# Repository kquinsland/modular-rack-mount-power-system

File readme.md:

# Modular Rack Power

This is a "side-quest" project on the way to building a small "mini rack" dedicated to hosting GH/A runners.

I'll do the CAD and standalone development here before integrating it into the larger project.
The goal is to have a modular system of a backplane and multiple carrier modules that can be swapped in and out to provide different power configurations as needed.
As long as the power supply can handle it, backplanes may share/daisy-chain the
input distribution needed by their carrier modules.

Hardware, firmware, and host tooling for a modular mini-rack power system.

## Boards

- `backplane`: STM32C092/CAN-FD backplane with six carrier slots, power
  distribution, aggregate current monitoring, fan control, and a status
  NeoPixel.
- `carrier`: Mates with one backplane slot and hosts an SW3538 USB-C PD module.

Every backplane and carrier is an independent STM32C092 CAN-FD node. There is no
I2C mux and no controller/proxy relationship between nodes. Earlier hardware and
firmware were research prototypes and are not compatibility targets.

## Layout

```text
firmware/
  Cargo.toml
  backplane/
  carrier/
  bootloader/
  crates/
  tools/
  xtask/
  docs/pdcan/
hardware/
  boards/
    backplane/
    carrier/
  libraries/
    symbols/
    footprints/
    3dmodels/
  mechanical/
docs/
scripts/
build/
releases/
```

`build/` is for generated local outputs. `releases/` is for fabrication packages that should be preserved exactly as sent to a board house.

See [`firmware/README.md`](firmware/README.md) for workspace commands and the
current hardware/firmware contract. Run `mise run firmware:check` from this
directory, or run Cargo commands from `firmware/`. The reviewed implementation
plan is kept in [`firmware/plan.md`](firmware/plan.md).

## Documentation site

The public-facing project documentation is maintained in [`site/`](site/) and
is intended for <https://mrps.karlquinsland.com/>. Run `mise run site:serve` for
local preview or `mise run site:build` for a production build. Create journal
entries with `mise run worklog:new -- "Concise Summary"` to create
`site/content/worklogs/YYYY/MM/DD - Concise Summary/index.md` with matching
front matter and an adjacent `_files/` directory for page resources.

## Misc

I can't believe that it's STILL such a pain in the ass to use LCSC to search for parts that are stocked by the SMT service.
https://yaqwsx.github.io/jlcparts/#/

Also super useful reference: https://www.tinkervault.com/usb-power-sources/dc-pd30-adapters
It's how I 'caught' that the `sw3538` based module I am using is non-standard 140W, later confirmed:

- https://en.eeworld.com.cn/Reference_Designs/detail/81702
- https://github.com/happyme531/h1_SW35xx/issues/13#issuecomment-4361605621

https://github.com/Shrike-Lab/HomeLab-PDU-V1/blob/main/ASSEMBLY/README.md#pcb-tray

Plan was to use APK43070 but they do not support MCU controlling it via i2c

https://meron33.hatenablog.com/entry/2026/02/07/112759

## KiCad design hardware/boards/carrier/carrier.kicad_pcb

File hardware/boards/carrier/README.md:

# Carrier PCB

KiCad project for one mini-rack power carrier board.

Responsibilities:

- Mate with one backplane slot.
- Host one fixed-address DC/USB-C PD module.
- Convert the slot-local DC and CAN-FD interface into the module-local wiring.
- Keep carrier-side interfaces reusable across all backplane slots.

Assembly notes:

- `J1` and `MOD1` are intentionally DNP/excluded from the PCB assembly BOM. The
  user installs and solders the right-angle XT30PW(2+2) connector and SW3538
  module after assembly.
- The housekeeping converter shares the backplane's LM5164DDAR regulator and
  PSPMAA0805-101M-ANP 100 µH inductor.
- L1 is placed and routed. The checked-in assembly and fabrication outputs are
  generated and validated with `mise run production:carrier`.

Relevant docs:

- `../../../docs/system-overview.md`
- `../../../docs/interfaces.md`
- `../../../docs/power-budget.md`
- `hardware-handoff.md`

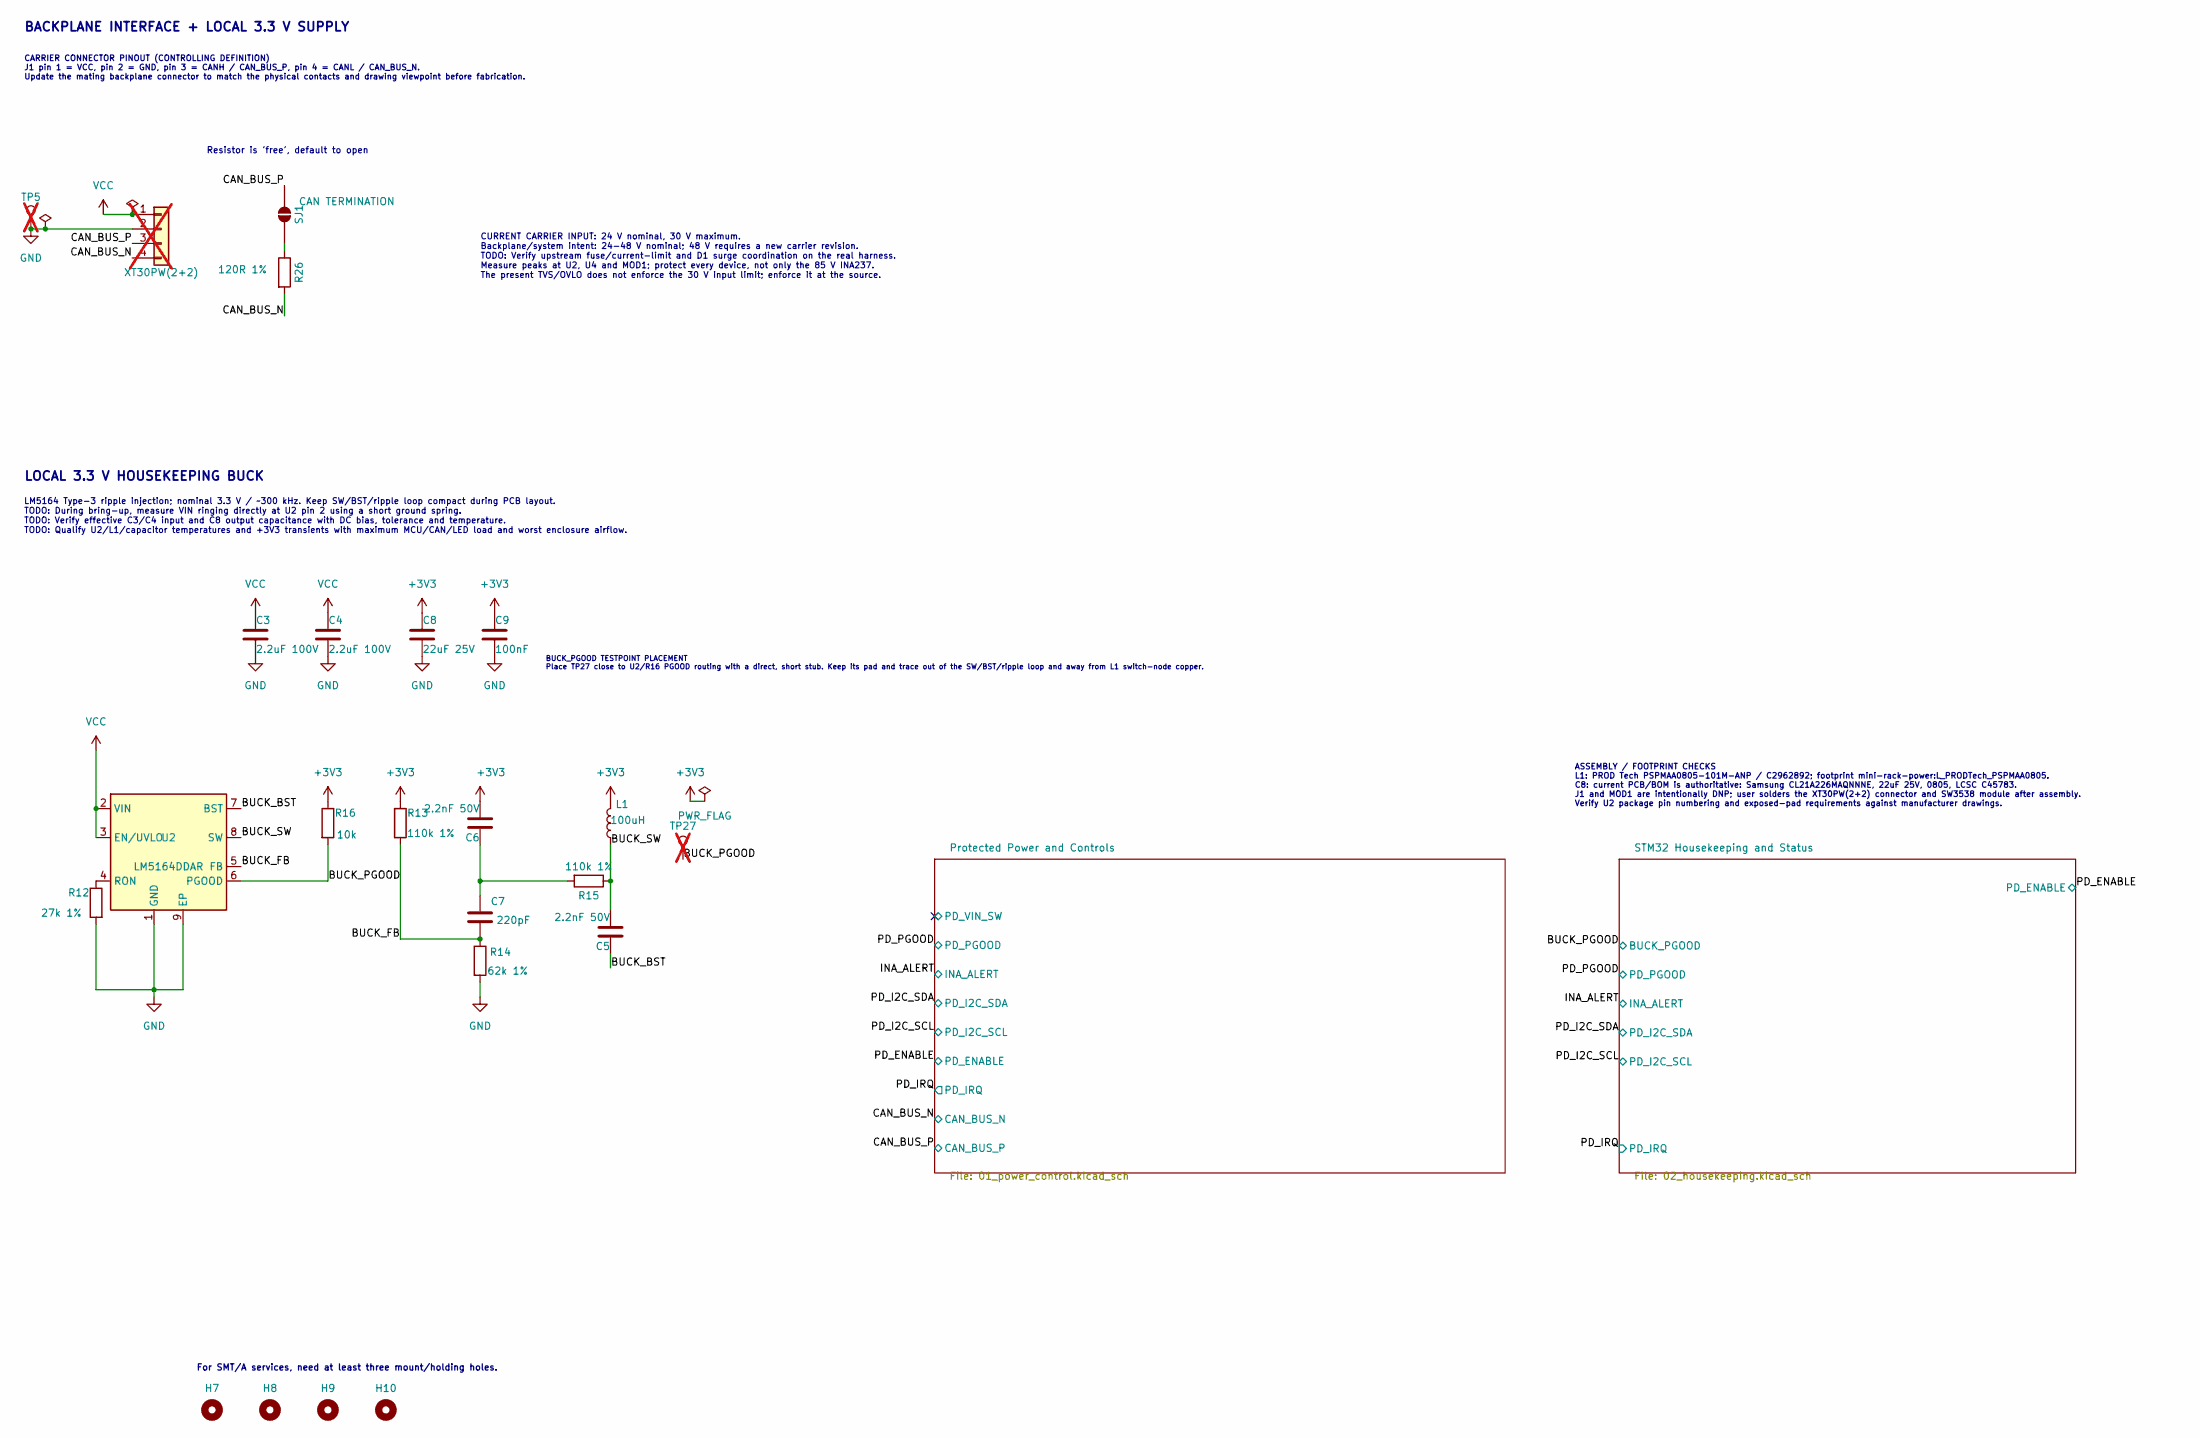
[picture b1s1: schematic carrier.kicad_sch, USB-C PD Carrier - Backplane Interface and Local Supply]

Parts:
C3, C4: 2.2uF 100V; C_1210_3225Metric; MPN CL32B225KCJSNNE; LCSC C55151
C5, C6: 2.2nF 50V; C_0603_1608Metric; MPN 0603B222K500NT; LCSC C1604
C7: 220pF; C_0603_1608Metric; MPN CC0603JRNPO9BN221; LCSC C106210
C8: 22uF 25V; C_0805_2012Metric; MPN CL21A226MAQNNNE; LCSC C45783
C9: 100nF; C_0603_1608Metric; MPN CC0603KRX7R9BB104; LCSC C14663
H7, H8, H9, H10: ToolingHole_1.152mm; MountingHole_JLCPCB_Tooling_1.152mm
J1: XT30PW(2+2); Amass_XT30PW_2plus2_M_RightAngle_THT; MPN XT30PW(2+2)-M.G.B; LCSC C19268030; not fitted
L1: 100uH; L_PRODTech_PSPMAA0805; MPN PSPMAA0805-101M-ANP; LCSC C2962892
R12: 27k 1%; R_0603_1608Metric; MPN 0603WAF2702T5E; LCSC C22967
R13, R15: 110k 1%; R_0603_1608Metric; MPN 0603WAF1103T5E; LCSC C25805
R14: 62k 1%; R_0603_1608Metric; MPN 0603WAF6202T5E; LCSC C23221
R16: 10k; R_0603_1608Metric; MPN 0603WAF1002T5E; LCSC C25804
R26: 120R 1%; R_0603_1608Metric; MPN 0603WAF1200T5E; LCSC C22787
SJ1: CAN TERMINATION; SolderJumper-2_P1.3mm_Open_Pad1.0x1.5mm; MPN PCB feature
TP5: GND; TestPoint_Pad_D1.0mm; not fitted
TP27: BUCK_PGOOD; TestPoint_Pad_D1.5mm; MPN PCB test point; not fitted
U2: LM5164DDAR; TI_SO-PowerPAD-8; MPN LM5164DDAR; LCSC C477928

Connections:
+3V3: C6.2, C8.1, C9.1, L1.2, R13.1, R16.1; also elsewhere on the board
/BUCK_BST: C5.1, U2.7 (BST)
/BUCK_FB: C7.2, R13.2, R14.1, U2.5 (FB)
/BUCK_PGOOD: R16.2, TP27.1 (1_1), U2.6 (PGOOD); also elsewhere on the board
/BUCK_SW: C5.2, L1.1, R15.1, U2.8 (SW)
/CAN_BUS_N: J1.4, R26.2; also elsewhere on the board
/CAN_BUS_P: J1.3, SJ1.1 (A); also elsewhere on the board
GND: C3.2, C4.2, C8.2, C9.2, J1.2, R12.2, R14.2, TP5.1 (1_1), U2.1 (GND), U2.9 (EP); also elsewhere on the board
unnamed: C6.1, C7.1, R15.2
unnamed: R26.1, SJ1.2 (B)
unnamed: R12.1, U2.4 (RON)
VCC: C3.1, C4.1, J1.1, U2.2 (VIN), U2.3 (EN/UVLO); also elsewhere on the board

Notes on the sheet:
CURRENT CARRIER INPUT: 24 V nominal, 30 V maximum. Backplane/system intent: 24-48 V nominal; 48 V requires a new carrier revision. TODO: Verify upstream fuse/current-limit and D1 surge coordination on the real harness. Measure peaks at U2, U4 and MOD1; protect every device, not only the 85 V INA237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
LOCAL 3.3 V HOUSEKEEPING BUCK
ASSEMBLY / FOOTPRINT CHECKS L1: PROD Tech PSPMAA0805-101M-ANP / C2962892; footprint mini-rack-power:L_PRODTech_PSPMAA0805. C8: current PCB/BOM is authoritative: Samsung CL21A226MAQNNNE, 22uF 25V, 0805, LCSC C45783. J1 and MOD1 are intentionally DNP; user solders the XT30PW(2+2) connector and SW3538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
Resistor is 'free', default to open
LM5164 Type-3 ripple injection; nominal 3.3 V / ~300 kHz. Keep SW/BST/ripple loop compact during PCB layout. TODO: During bring-up, measure VIN ringing directly at U2 pin 2 using a short ground spring. TODO: Verify effective C3/C4 input and C8 output capacitance with DC bias, tolerance and temperat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
BUCK_PGOOD TESTPOINT PLACEMENT Place TP27 close to U2/R16 PGOOD routing with a direct, short stub. Keep its pad and trace out of the SW/BST/ripple loop and away from L1 switch-node copper.
For SMT/A services, need at least three mount/holding holes.
CARRIER CONNECTOR PINOUT (CONTROLLING DEFINITION) J1 pin 1 = VCC, pin 2 = GND, pin 3 = CANH / CAN_BUS_P, pin 4 = CANL / CAN_BUS_N. Update the mating backplane connector to match the physical contacts and drawing viewpoint before fabrication.
BACKPLANE INTERFACE + LOCAL 3.3 V SUPPLY

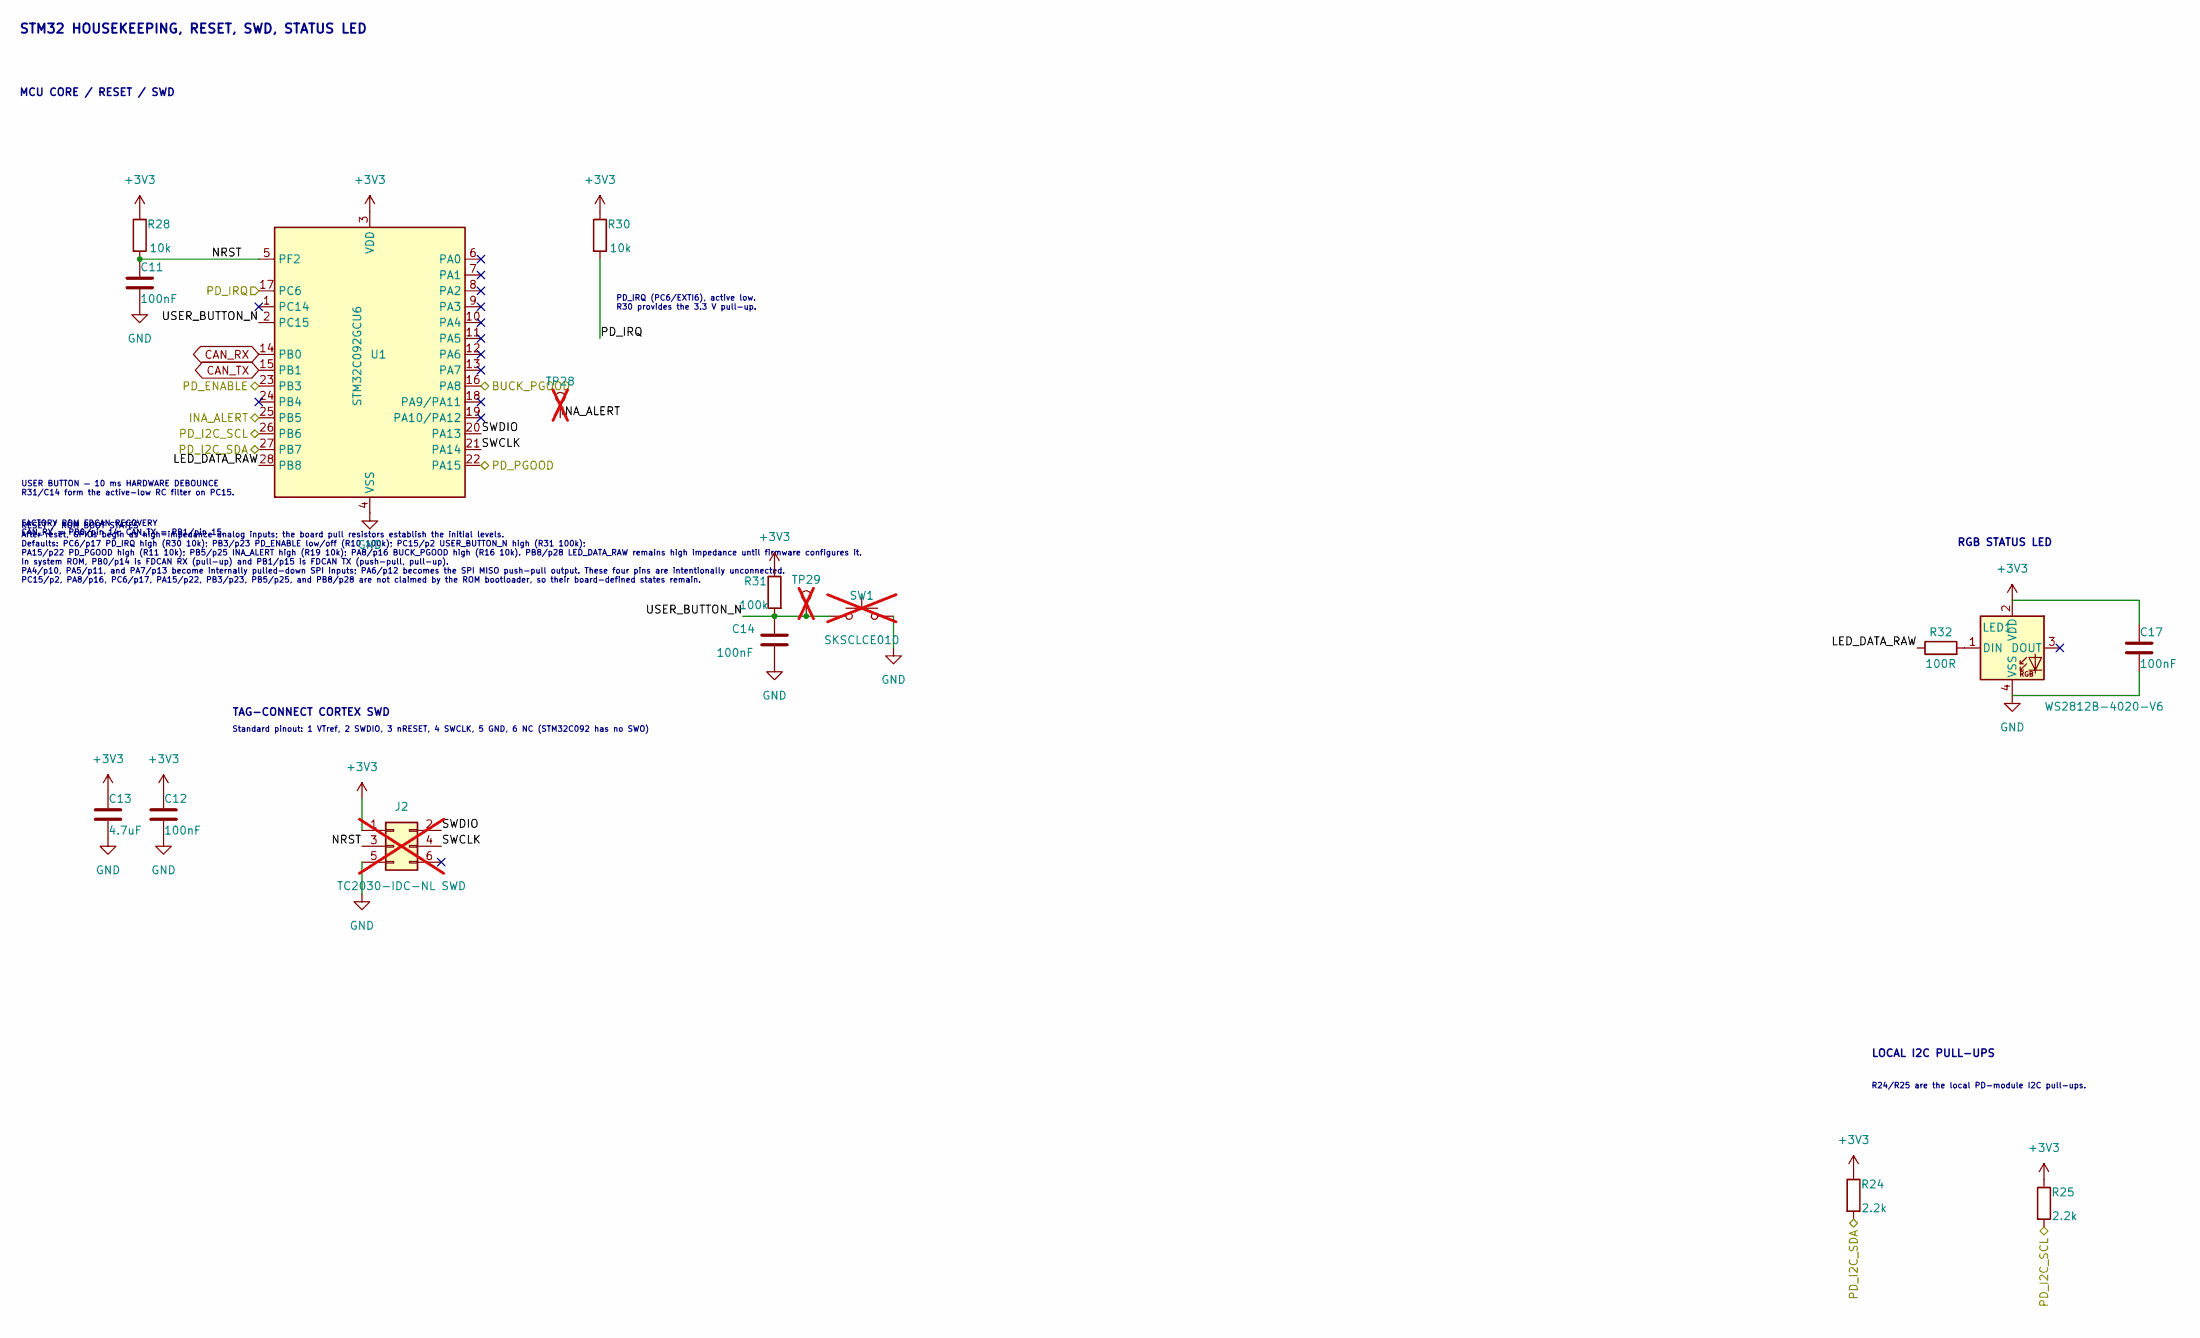
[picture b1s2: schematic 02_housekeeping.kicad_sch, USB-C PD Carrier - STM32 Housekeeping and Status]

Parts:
C11, C12, C14, C17: 100nF; C_0603_1608Metric; MPN CC0603KRX7R9BB104; LCSC C14663
C13: 4.7uF; C_0603_1608Metric; MPN CL10A475KO8NNNC; LCSC C19666
J2: TC2030-IDC-NL SWD; Tag-Connect_TC2030-IDC-NL_2x03_P1.27mm_Vertical; MPN TC2030-IDC-NL; not fitted
LED1: WS2812B-4020-V6; LED_Worldsemi_WS2812B-4020-V6_SideView; MPN WS2812B-4020-V6; LCSC C52941387
R24, R25: 2.2k; R_0603_1608Metric; MPN 0603WAF2201T5E; LCSC C4190
R28, R30: 10k; R_0603_1608Metric; MPN 0603WAF1002T5E; LCSC C25804
R31: 100k; R_0603_1608Metric; MPN 0603WAF1003T5E; LCSC C25803
R32: 100R; R_0603_1608Metric; MPN 0603WAF1000T5E; LCSC C22775
SW1: SKSCLCE010; SW_ALPS_SKSCLCE010_SidePush; MPN SKSCLCE010; LCSC C139799; not fitted
TP28: INA_ALERT; TestPoint_Pad_D1.5mm; MPN PCB test point; not fitted
TP29: USER_BUTTON_N; TestPoint_Pad_D1.5mm; MPN PCB test point; not fitted
U1: STM32C092GCU6; QFN-28_4x4mm_P0.5mm; MPN STM32C092GCU6; LCSC C44847705

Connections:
+3V3: C12.1, C13.1, C17.1, J2.1, LED1.2 (VDD), R24.1, R25.1, R28.1, R30.1, R31.1, U1.3 (VDD); also elsewhere on the board
/BUCK_PGOOD: U1.16 (PA8); also elsewhere on the board
/INA_ALERT: TP28.1 (1_1), U1.25 (PB5); also elsewhere on the board
/PD_ENABLE: U1.23 (PB3); also elsewhere on the board
/PD_I2C_SCL: R25.2, U1.26 (PB6); also elsewhere on the board
/PD_I2C_SDA: R24.2, U1.27 (PB7); also elsewhere on the board
/PD_IRQ: R30.2, U1.17 (PC6); also elsewhere on the board
/PD_PGOOD: U1.22 (PA15); also elsewhere on the board
/STM32 Housekeeping and Status/LED_DATA_RAW: R32.1, U1.28 (PB8)
/STM32 Housekeeping and Status/NRST: C11.1, J2.3, R28.2, U1.5 (PF2)
/STM32 Housekeeping and Status/SWCLK: J2.4, U1.21 (PA14)
/STM32 Housekeeping and Status/SWDIO: J2.2, U1.20 (PA13)
/STM32 Housekeeping and Status/USER_BUTTON_N: C14.1, R31.2, SW1.2, TP29.1 (1_1), U1.2 (PC15)
CAN_RX: U1.14 (PB0); also elsewhere on the board
CAN_TX: U1.15 (PB1); also elsewhere on the board
GND: C11.2, C12.2, C13.2, C14.2, C17.2, J2.5, LED1.4 (VSS), SW1.1, U1.4 (VSS); also elsewhere on the board
unnamed: LED1.1 (DIN), R32.2

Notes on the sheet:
Standard pinout: 1 VTref, 2 SWDIO, 3 nRESET, 4 SWCLK, 5 GND, 6 NC (STM32C092 has no SWO)
FACTORY ROM FDCAN RECOVERY CAN_RX = PB0/pin 14; CAN_TX = PB1/pin 15.
LOCAL I2C PULL-UPS
USER BUTTON — 10 ms HARDWARE DEBOUNCE R31/C14 form the active-low RC filter on PC15.
R24/R25 are the local PD-module I2C pull-ups.
TAG-CONNECT CORTEX SWD
MCU CORE / RESET / SWD
STM32 HOUSEKEEPING, RESET, SWD, STATUS LED
PD_IRQ (PC6/EXTI6), active low. R30 provides the 3.3 V pull-up.
RESET / ROM BOOT STATES After reset, GPIOs begin as high-impedance analog inputs; the board pull resistors establish the initial levels. Defaults: PC6/p17 PD_IRQ high (R30 10k); PB3/p23 PD_ENABLE low/off (R10 100k); PC15/p2 USER_BUTTON_N high (R31 100k); PA15/p22 PD_PGOOD high (R11 10k); PB5/p25 IN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
RGB STATUS LED

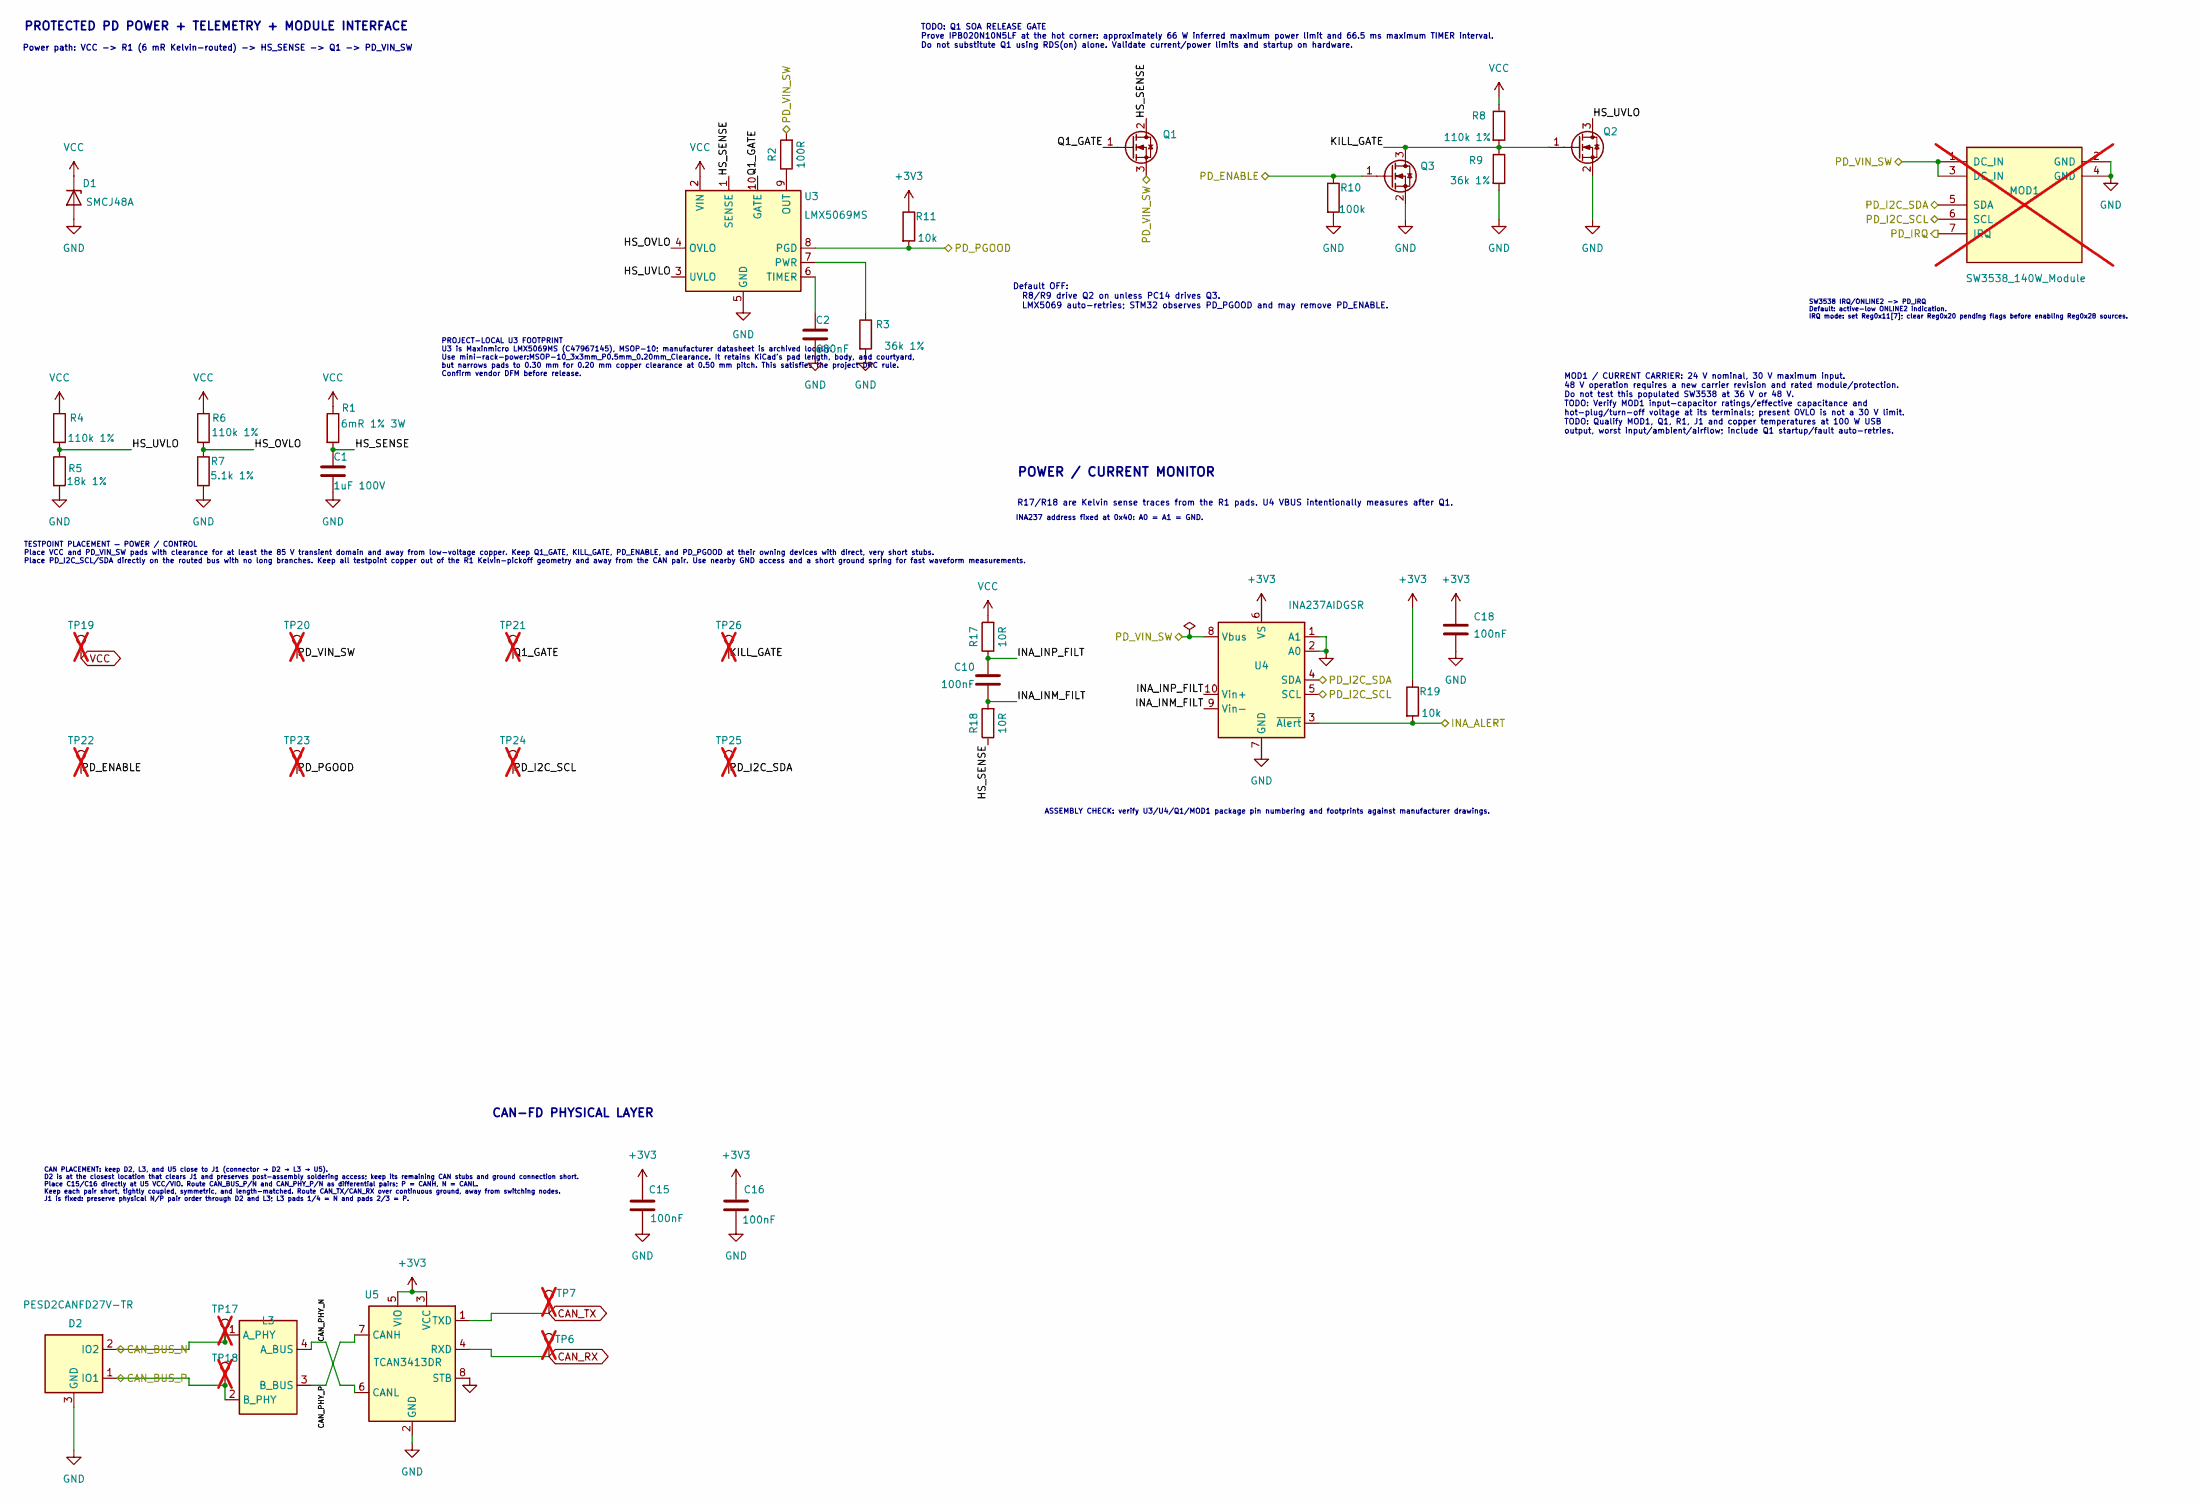
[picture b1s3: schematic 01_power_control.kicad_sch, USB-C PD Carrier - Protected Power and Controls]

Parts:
C1: 1uF 100V; C_1206_3216Metric; MPN CL31B105KCHNNNE; LCSC C13832
C2: 680nF; C_0603_1608Metric; MPN 0603B684K160NT; LCSC C24797
C10, C15, C16, C18: 100nF; C_0603_1608Metric; MPN CC0603KRX7R9BB104; LCSC C14663
D1: SMCJ48A; D_SMC_Silk0.15mm; MPN SMCJ48A; LCSC C19077611
D2: PESD2CANFD27V-TR; SOT-23; MPN PESD2CANFD27V-TR; LCSC C552488
L3: ACT1210D-101-2P-TL00; L_CommonModeChoke_TDK_ACT1210D; MPN ACT1210D-101-2P-TL00; LCSC C3039743
MOD1: SW3538_140W_Module; not fitted
Q1: IPB020N10N5LF; TO-263-3_TabPin2; MPN IPB020N10N5LF; LCSC C536484
Q2, Q3: 2N7002; SOT-23; MPN 2N7002; LCSC C8545
R1: 6mR 1% 3W; R_2512_6332Metric; MPN HoLLR2512-3W-6mR-1%; LCSC C2985709
R2: 100R; R_0603_1608Metric; MPN 0603WAF1000T5E; LCSC C22775
R3, R9: 36k 1%; R_0603_1608Metric; MPN 0603WAF3602T5E; LCSC C23147
R4, R6, R8: 110k 1%; R_0603_1608Metric; MPN 0603WAF1103T5E; LCSC C25805
R5: 18k 1%; R_0603_1608Metric; MPN 0603WAF1802T5E; LCSC C25810
R7: 5.1k 1%; R_0603_1608Metric; MPN 0603WAF5101T5E; LCSC C23186
R10: 100k; R_0603_1608Metric; MPN 0603WAF1003T5E; LCSC C25803
R11, R19: 10k; R_0603_1608Metric; MPN 0603WAF1002T5E; LCSC C25804
R17, R18: 10R; R_0603_1608Metric; MPN 0603WAF100JT5E; LCSC C22859
TP6: CAN_RX; TestPoint_Pad_D1.5mm; MPN PCB test point; not fitted
TP7: CAN_TX; TestPoint_Pad_D1.5mm; MPN PCB test point; not fitted
TP17: CAN_BUS_N; TestPoint_Pad_D1.5mm; MPN PCB test point; not fitted
TP18: CAN_BUS_P; TestPoint_Pad_D1.5mm; MPN PCB test point; not fitted
TP19: VCC; TestPoint_Pad_D1.5mm; MPN PCB test point; not fitted
TP20: PD_VIN_SW; TestPoint_Pad_D1.5mm; MPN PCB test point; not fitted
TP21: Q1_GATE; TestPoint_Pad_D1.5mm; MPN PCB test point; not fitted
TP22: PD_ENABLE; TestPoint_Pad_D1.5mm; MPN PCB test point; not fitted
TP23: PD_PGOOD; TestPoint_Pad_D1.5mm; MPN PCB test point; not fitted
TP24: PD_I2C_SCL; TestPoint_Pad_D1.5mm; MPN PCB test point; not fitted
TP25: PD_I2C_SDA; TestPoint_Pad_D1.5mm; MPN PCB test point; not fitted
TP26: KILL_GATE; TestPoint_Pad_D1.5mm; MPN PCB test point; not fitted
U3: LMX5069MS; MSOP-10_3x3mm_P0.5mm_0.20mm_Clearance; MPN LMX5069MS; LCSC C47967145
U4: INA237AIDGSR; TSSOP-10_3x3mm_P0.5mm; MPN INA237AIDGSR; LCSC C2864837
U5: TCAN3413DR; SOIC-8_3.9x4.9mm_P1.27mm; MPN TCAN3413DR; LCSC C22433320

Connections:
+3V3: C15.1, C16.1, C18.1, R11.1, R19.1, U4.6 (VS), U5.3 (VCC), U5.5 (VIO); also elsewhere on the board
/CAN_BUS_N: D2.2 (IO2), L3.1 (A_PHY), TP17.1 (1_1); also elsewhere on the board
/CAN_BUS_P: D2.1 (IO1), L3.2 (B_PHY), TP18.1 (1_1); also elsewhere on the board
/INA_ALERT: R19.2, U4.3 (~Alert); also elsewhere on the board
/PD_ENABLE: Q3.1 (G), R10.1, TP22.1 (1_1); also elsewhere on the board
/PD_I2C_SCL: MOD1.6 (SCL), TP24.1 (1_1), U4.5 (SCL); also elsewhere on the board
/PD_I2C_SDA: MOD1.5 (SDA), TP25.1 (1_1), U4.4 (SDA); also elsewhere on the board
/PD_IRQ: MOD1.7 (IRQ); also elsewhere on the board
/PD_PGOOD: R11.2, TP23.1 (1_1), U3.8 (PGD); also elsewhere on the board
/Protected Power and Controls/CAN_PHY_N: L3.4 (A_BUS), U5.6 (CANL)
/Protected Power and Controls/CAN_PHY_P: L3.3 (B_BUS), U5.7 (CANH)
/Protected Power and Controls/HS_OVLO: R6.2, R7.1, U3.4 (OVLO)
/Protected Power and Controls/HS_SENSE: C1.1, Q1.2 (D), R1.2, R18.1, U3.1 (SENSE)
/Protected Power and Controls/HS_UVLO: Q2.3 (D), R4.2, R5.1, U3.3 (UVLO)
/Protected Power and Controls/INA_INM_FILT: C10.2, R18.2, U4.9 (Vin-)
/Protected Power and Controls/INA_INP_FILT: C10.1, R17.1, U4.10 (Vin+)
/Protected Power and Controls/KILL_GATE: Q2.1 (G), Q3.3 (D), R8.2, R9.1, TP26.1 (1_1)
/Protected Power and Controls/PD_VIN_SW: MOD1.1 (DC_IN), MOD1.3 (DC_IN), Q1.3 (S), R2.2, TP20.1 (1_1), U4.8 (Vbus)
/Protected Power and Controls/Q1_GATE: Q1.1 (G), TP21.1 (1_1), U3.10 (GATE)
CAN_RX: TP6.1 (1_1), U5.4 (RXD); also elsewhere on the board
CAN_TX: TP7.1 (1_1), U5.1 (TXD); also elsewhere on the board
GND: C1.2, C2.2, C15.2, C16.2, C18.2, D1.2 (A), D2.3 (GND), MOD1.2 (GND), MOD1.4 (GND), Q2.2 (S), Q3.2 (S), R3.2, R5.2, R7.2, R9.2, R10.2, U3.5 (GND), U4.1 (A1), U4.2 (A0), U4.7 (GND), U5.2 (GND), U5.8 (STB); also elsewhere on the board
unnamed: R2.1, U3.9 (OUT)
unnamed: R3.1, U3.7 (PWR)
unnamed: C2.1, U3.6 (TIMER)
VCC: D1.1 (K), R1.1, R4.1, R6.1, R8.1, R17.2, TP19.1 (1_1), U3.2 (VIN); also elsewhere on the board

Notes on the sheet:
MOD1 / CURRENT CARRIER: 24 V nominal, 30 V maximum input. 48 V operation requires a new carrier revision and rated module/protection. Do not test this populated SW3538 at 36 V or 48 V. TODO: Verify MOD1 input-capacitor ratings/effective capacitance and hot-plug/turn-off voltage at its terminals; pr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
PROTECTED PD POWER + TELEMETRY + MODULE INTERFACE
INA237 address fixed at 0x40: A0 = A1 = GND.
TODO: Q1 SOA RELEASE GATE Prove IPB020N10N5LF at the hot corner: approximately 66 W inferred maximum power limit and 66.5 ms maximum TIMER interval. Do not substitute Q1 using RDS(on) alone. Validate current/power limits and startup on hardware.
R17/R18 are Kelvin sense traces from the R1 pads. U4 VBUS intentionally measures after Q1.
TESTPOINT PLACEMENT — POWER / CONTROL Place VCC and PD_VIN_SW pads with clearance for at least the 85 V transient domain and away from low-voltage copper. Keep Q1_GATE, KILL_GATE, PD_ENABLE, and PD_PGOOD at their owning devices with direct, very short stubs. Place PD_I2C_SCL/SDA directly on the rou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
PROJECT-LOCAL U3 FOOTPRINT U3 is Maxinmicro LMX5069MS (C47967145), MSOP-10; manufacturer datasheet is archived locally. Use mini-rack-power:MSOP-10_3x3mm_P0.5mm_0.20mm_Clearance. It retains KiCad's pad length, body, and courtyard, but narrows pads to 0.30 mm for 0.20 mm copper clearance at 0.50 mm 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
Default OFF: R8/R9 drive Q2 on unless PC14 drives Q3. LMX5069 auto-retries; STM32 observes PD_PGOOD and may remove PD_ENABLE.
CAN-FD PHYSICAL LAYER
CAN PLACEMENT: keep D2, L3, and U5 close to J1 (connector → D2 → L3 → U5). D2 is at the closest location that clears J1 and preserves post-assembly soldering access; keep its remaining CAN stubs and ground connection short. Place C15/C16 directly at U5 VCC/VIO. Route CAN_BUS_P/N and CAN_PHY_P/N as 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
SW3538 IRQ/ONLINE2 -> PD_IRQ Default: active-low ONLINE2 indication. IRQ mode: set Reg0x11[7]; clear Reg0x20 pending flags before enabling Reg0x28 sources.
ASSEMBLY CHECK: verify U3/U4/Q1/MOD1 package pin numbering and footprints against manufacturer drawings.
Power path: VCC -> R1 (6 mR Kelvin-routed) -> HS_SENSE -> Q1 -> PD_VIN_SW
POWER / CURRENT MONITOR

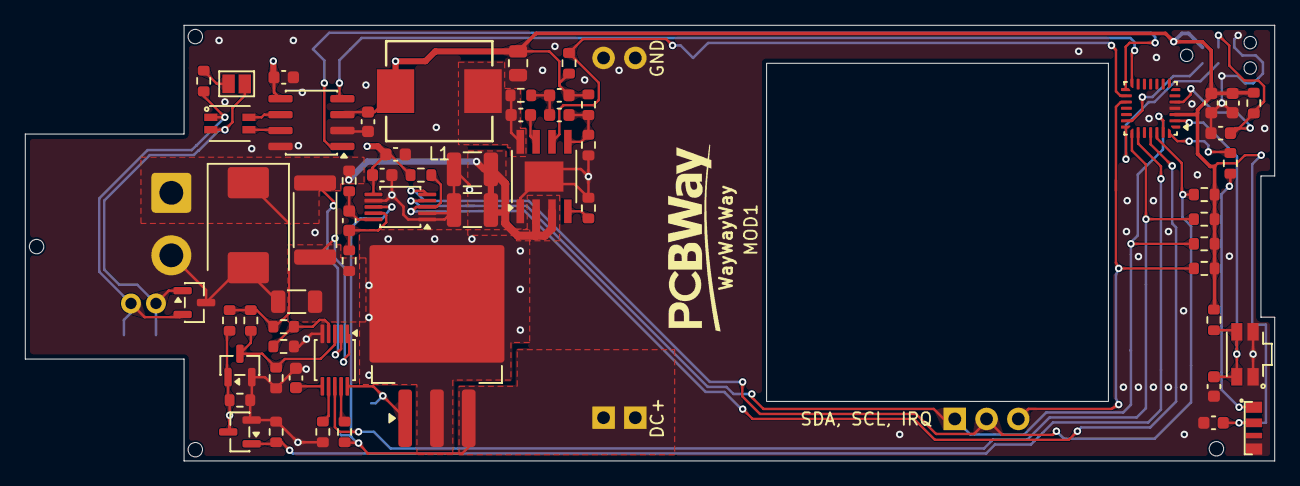
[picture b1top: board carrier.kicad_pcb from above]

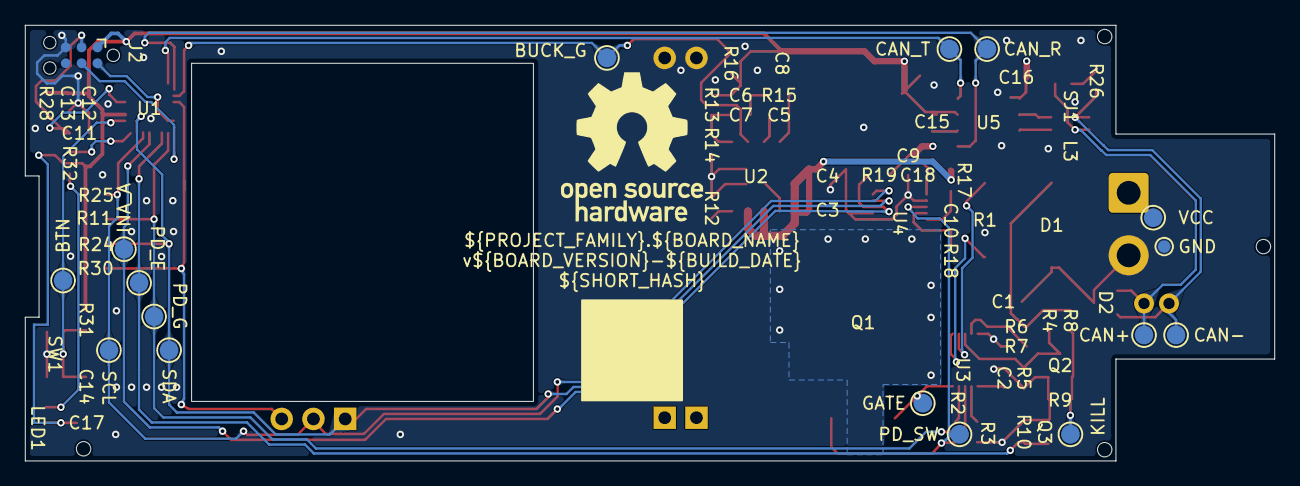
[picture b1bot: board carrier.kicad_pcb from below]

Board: 4 copper layers, 100.0 x 34.9 mm, 83 parts (17 on the bottom side), 39 nets.

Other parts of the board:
LOGO_PCBWAY: PCBWay_Logo_15mm

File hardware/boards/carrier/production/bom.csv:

Designator,Footprint,Quantity,Value,LCSC Part #
C1,C_1206_3216Metric,1,1uF 100V,C13832
C2,C_0603_1608Metric,1,680nF,C24797
"C3, C4",C_1210_3225Metric,2,2.2uF 100V,C55151
"C5, C6",C_0603_1608Metric,2,2.2nF 50V,C1604
C7,C_0603_1608Metric,1,220pF,C106210
C8,C_0805_2012Metric,1,22uF 25V,C45783
"C9, C10, C11, C12, C14, C15, C16, C17, C18",C_0603_1608Metric,9,100nF,C14663
C13,C_0603_1608Metric,1,4.7uF,C19666
D1,D_SMC_Silk0.15mm,1,SMCJ48A,C19077611
D2,SOT-23,1,PESD2CANFD27V-TR,C552488
L1,L_PRODTech_PSPMAA0805,1,100uH,C2962892
L3,L_CommonModeChoke_TDK_ACT1210D,1,ACT1210D-101-2P-TL00,C3039743
LED1,LED_Worldsemi_WS2812B-4020-V6_SideView,1,WS2812B-4020-V6,C52941387
Q1,TO-263-3_TabPin2,1,IPB020N10N5LF,C536484
"Q2, Q3",SOT-23,2,2N7002,C8545
R1,R_2512_6332Metric,1,6mR 1% 3W,C2985709
"R2, R32",R_0603_1608Metric,2,100R,C22775
"R3, R9",R_0603_1608Metric,2,36k 1%,C23147
"R4, R6, R8, R13, R15",R_0603_1608Metric,5,110k 1%,C25805
R5,R_0603_1608Metric,1,18k 1%,C25810
R7,R_0603_1608Metric,1,5.1k 1%,C23186
"R10, R31",R_0603_1608Metric,2,100k,C25803
"R11, R16, R19, R28, R30",R_0603_1608Metric,5,10k,C25804
R12,R_0603_1608Metric,1,27k 1%,C22967
R14,R_0603_1608Metric,1,62k 1%,C23221
"R17, R18",R_0603_1608Metric,2,10R,C22859
"R24, R25",R_0603_1608Metric,2,2.2k,C4190
R26,R_0603_1608Metric,1,120R 1%,C22787
U1,QFN-28_4x4mm_P0.5mm,1,STM32C092GCU6,C44847705
U2,TI_SO-PowerPAD-8,1,LM5164DDAR,C477928
U3,MSOP-10_3x3mm_P0.5mm_0.20mm_Clearance,1,LMX5069MS,C47967145
U4,TSSOP-10_3x3mm_P0.5mm,1,INA237AIDGSR,C2864837
U5,SOIC-8_3.9x4.9mm_P1.27mm,1,TCAN3413DR,C22433320

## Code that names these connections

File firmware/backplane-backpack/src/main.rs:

#![no_main]
#![no_std]

mod channels;
mod tasks;

use backplane_backpack_firmware::board::{
    CAN_DATA_BITRATE, CAN_NOMINAL_BITRATE, MUX_RESET_AVAILABLE,
};
use backplane_backpack_firmware::config_store::ConfigStore;
use backplane_backpack_firmware::config_store::stm32::Stm32ConfigFlash;
use backplane_backpack_firmware::fan::{FanDrive, THREE_WIRE_FREQUENCY_HZ_PROVISIONAL};
use backplane_backpack_firmware::status::STATUS_WORDS;
use backplane_backpack_firmware::supervisor::IWDG_TIMEOUT_US_PROVISIONAL;
use embassy_executor::Spawner;
use embassy_stm32::bind_interrupts;
use embassy_stm32::can::config::{GlobalFilter, NonMatchingFilter};
use embassy_stm32::can::{self, CanConfigurator};
use embassy_stm32::dma;
use embassy_stm32::gpio::{Level, Output, OutputType, Pull, Speed};
use embassy_stm32::i2c::{self, I2c};
use embassy_stm32::peripherals;
use embassy_stm32::rcc::{Hsi, HsiKerDiv, HsiSysDiv};
use embassy_stm32::time::Hertz;
use embassy_stm32::timer;
use embassy_stm32::timer::input_capture::{CapturePin, InputCapture};
use embassy_stm32::timer::low_level::CountingMode;
use embassy_stm32::timer::simple_pwm::{PwmPin, SimplePwm};
use embassy_stm32::wdg::IndependentWatchdog;
use embassy_time::{Duration, Timer};
use panic_halt as _;
use pdcan_protocol::ResetFlags;
use pdcan_types::{NodeUid, PersistentSettings};
use static_cell::StaticCell;

const I2C_FREQUENCY_HZ: u32 = 100_000;
const I2C_TIMEOUT_MS_PROVISIONAL: u64 = 100;
const TACH_TIMER_HZ_PROVISIONAL: u32 = 1_000_000;
const WS2812_TIMER_HZ: u32 = 800_000;
const STATUS_DMA_CAPACITY: usize = STATUS_WORDS + 8;

static STATUS_DMA_BUFFER: StaticCell<[u16; STATUS_DMA_CAPACITY]> = StaticCell::new();

bind_interrupts!(struct Irqs {
    FDCAN1_IT0 => can::IT0InterruptHandler<peripherals::FDCAN1>;
    FDCAN1_IT1 => can::IT1InterruptHandler<peripherals::FDCAN1>;
    I2C2 => i2c::EventInterruptHandler<peripherals::I2C2>, i2c::ErrorInterruptHandler<peripherals::I2C2>;
    DMA1_CHANNEL1 => dma::InterruptHandler<peripherals::DMA1_CH1>;
    DMA1_CHANNEL2_3 => dma::InterruptHandler<peripherals::DMA1_CH2>, dma::InterruptHandler<peripherals::DMA1_CH3>;
    TIM17 => timer::CaptureCompareInterruptHandler<peripherals::TIM17>;
});

#[embassy_executor::main]
async fn main(spawner: Spawner) -> ! {
    let mut config = embassy_stm32::Config::default();
    config.rcc.hsi = Some(Hsi {
        sys_div: HsiSysDiv::DIV1,
        ker_div: HsiKerDiv::DIV1,
    });
    let p = embassy_stm32::init(config);
    let reset_flags = capture_reset_flags();

    // Rev B presents only upstream I2C, 3.3 V, and ground at the backplane
    // boundary. Its backplane-local TCA9548A reset is not MCU-controlled, and
    // the PCA9554 gate pull-downs hold every slot off at cold power-on.
    let mux_reset = if MUX_RESET_AVAILABLE {
        let mut reset = Output::new(p.PA3, Level::Low, Speed::Low);
        Timer::after_millis(1).await;
        reset.set_high();
        Some(reset)
    } else {
        None
    };
    let can_standby = Output::new(p.PA4, Level::High, Speed::Low);

    let mut fan_pwm = SimplePwm::new(
        p.TIM2,
        Some(PwmPin::new(p.PA0, OutputType::PushPull)),
        None,
        None,
        None,
        Hertz::hz(THREE_WIRE_FREQUENCY_HZ_PROVISIONAL),
        CountingMode::EdgeAlignedUp,
    );
    {
        let mut channel = fan_pwm.ch1();
        channel.set_duty_cycle_percent(FanDrive::BOOT_SAFE.pa0_high_percent);
        channel.enable();
    }
    let fan_tach = InputCapture::new(
        p.TIM17,
        Some(CapturePin::new(p.PA1, Pull::None)),
        None,
        None,
        None,
        Irqs,
        Hertz::hz(TACH_TIMER_HZ_PROVISIONAL),
        CountingMode::EdgeAlignedUp,
    );

    let status_pwm = SimplePwm::new(
        p.TIM15,
        Some(PwmPin::new(p.PA2, OutputType::PushPull)),
        None,
        None,
        None,
        Hertz::hz(WS2812_TIMER_HZ),
        CountingMode::EdgeAlignedUp,
    );
    let status_buffer = STATUS_DMA_BUFFER.init([0; STATUS_DMA_CAPACITY]);
    let status_output =
        status_pwm
            .split()
            .ch1
            .into_ring_buffered_channel(p.DMA1_CH3, status_buffer, Irqs);

    let mut i2c_config = i2c::Config::default();
    i2c_config.frequency = Hertz::hz(I2C_FREQUENCY_HZ);
    i2c_config.timeout = Duration::from_millis(I2C_TIMEOUT_MS_PROVISIONAL);
    let pd_bus = I2c::new(
        p.I2C2, p.PA7, p.PA6, p.DMA1_CH1, p.DMA1_CH2, Irqs, i2c_config,
    );

    let mut can_configurator = CanConfigurator::new(p.FDCAN1, p.PA11, p.PA12, Irqs);
    can_configurator.set_bitrate(CAN_NOMINAL_BITRATE);
    can_configurator.set_fd_data_bitrate(CAN_DATA_BITRATE, false);
    let can_config = can_configurator.config().set_global_filter(
        GlobalFilter::reject_all().set_handle_extended_frames(NonMatchingFilter::IntoRxFifo0),
    );
    can_configurator.set_config(can_config);
    let can = can_configurator.into_normal_mode();

    let mut config_store = ConfigStore::new(Stm32ConfigFlash::new(p.FLASH));
    let settings = config_store
        .load()
        .ok()
        .flatten()
        .map_or(PersistentSettings::FACTORY_DEFAULT, |record| {
            record.settings
        });

    let watchdog = IndependentWatchdog::new(p.IWDG, IWDG_TIMEOUT_US_PROVISIONAL);

    spawner.spawn(tasks::status::status_task(status_output).unwrap());
    spawner.spawn(tasks::fan::fan_task(fan_pwm, fan_tach).unwrap());
    spawner.spawn(tasks::config::config_task(config_store).unwrap());
    let uid = NodeUid::from_bytes(embassy_stm32::uid::uid());
    spawner.spawn(tasks::pd_bus::pd_bus_task(pd_bus, mux_reset).unwrap());
    spawner.spawn(tasks::controller::controller_task(settings, uid, reset_flags).unwrap());
    spawner.spawn(tasks::can::can_task(can, can_standby).unwrap());
    spawner.spawn(tasks::supervisor::supervisor_task(watchdog).unwrap());

    loop {
        Timer::after_secs(60).await;
    }
}

fn capture_reset_flags() -> ResetFlags {
    let register = stm32_metapac::RCC.csr2().read();
    let mut flags = 0;
    if register.oblrstf() {
        flags |= ResetFlags::OPTION_BYTE;
    }
    if register.pinrstf() {
        flags |= ResetFlags::PIN;
    }
    if register.pwrrstf() {
        flags |= ResetFlags::POWER;
    }
    if register.sftrstf() {
        flags |= ResetFlags::SOFTWARE;
    }
    if register.iwdgrstf() {
        flags |= ResetFlags::INDEPENDENT_WATCHDOG;
    }
    if register.wwdgrstf() {
        flags |= ResetFlags::WINDOW_WATCHDOG;
    }
    if register.lpwrrstf() {
        flags |= ResetFlags::LOW_POWER;
    }
    stm32_metapac::RCC
        .csr2()
        .modify(|register| register.set_rmvf(true));
    ResetFlags::from_bits(flags)
}
